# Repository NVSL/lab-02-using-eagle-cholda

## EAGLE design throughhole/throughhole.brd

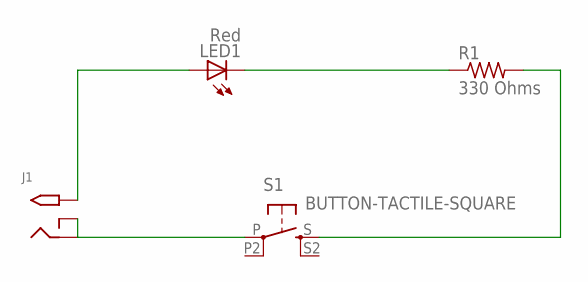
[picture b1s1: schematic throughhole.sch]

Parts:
J1: 2.1MMJACKTHM; PJ-102A
LED1: Red; LED5MM
R1: 330 Ohms; RESAD1160W55L680D260_HS
S1: BUTTON-TACTILE-SQUARE; BUTTON-TACTILE-SQUARE-ADAFRUIT1010

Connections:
unnamed: J1.RING, J1.RING_SW, S1.P
unnamed: R1.2, S1.S
unnamed: LED1.K (C), R1.1
unnamed: J1.TIP, LED1.A

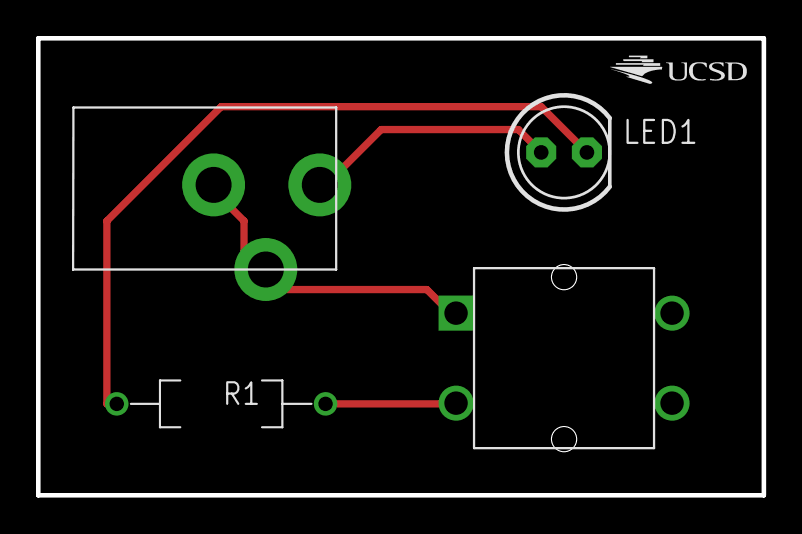
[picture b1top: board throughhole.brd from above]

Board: 2 copper layers, 40.3 x 25.4 mm, 5 parts (0 on the bottom side), 4 nets.

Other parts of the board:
U$1: UCS_LOGO

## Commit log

2016-04-07 lab 2 turnin
